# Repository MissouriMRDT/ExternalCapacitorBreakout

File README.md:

# ExternalCapacitorBreakout
Breakout board to hold external capacitors for the VESC

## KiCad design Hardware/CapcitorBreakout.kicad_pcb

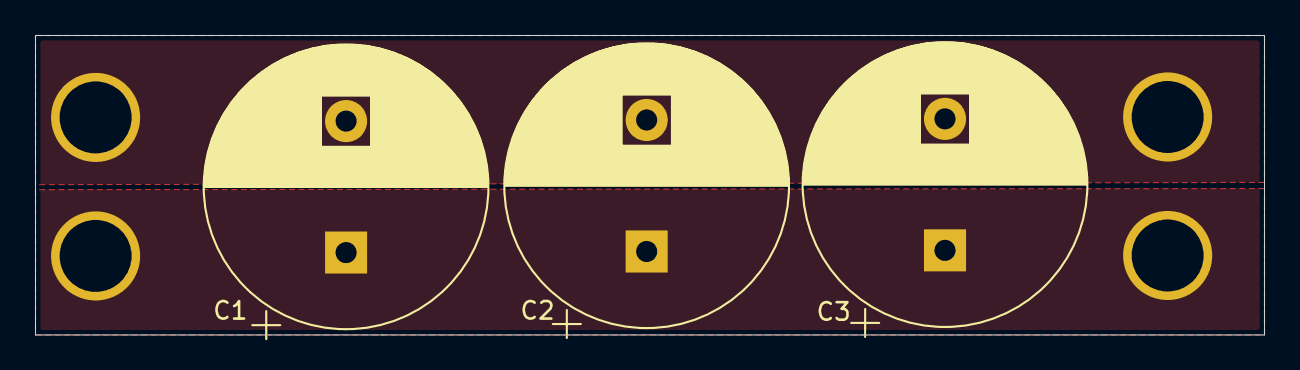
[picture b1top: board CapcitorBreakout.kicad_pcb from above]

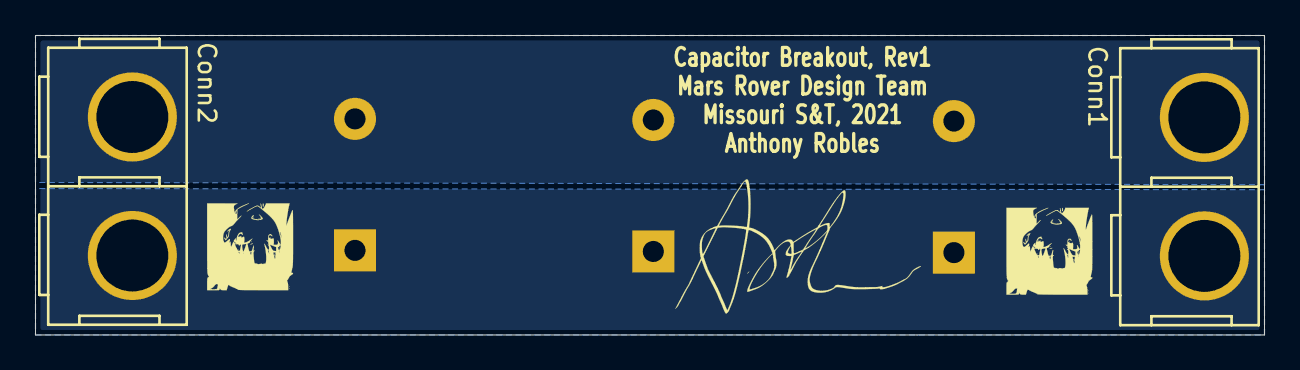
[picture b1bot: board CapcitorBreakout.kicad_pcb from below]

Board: 2 copper layers, 70.1 x 17.1 mm, 5 parts (2 on the bottom side), 2 nets, no tracks yet.

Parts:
C1, C2, C3: 680uF; CP_Radial_D16.0mm_P7.50mm
Conn1, Conn2: AndersonPP; Anderson_2_Vertical_Sidy_by_Side

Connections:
GND: C1.2, C2.2, C3.2, Conn1.1, Conn2.1
VS: C1.1, C2.1, C3.1, Conn1.2, Conn2.2

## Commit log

2021-02-16 Completed first rev of external capacitors breakout for VESCs
